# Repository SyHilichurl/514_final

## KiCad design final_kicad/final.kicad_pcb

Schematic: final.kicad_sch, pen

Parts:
BT1: Battery_Cell; JST_PH_B2B-PH-K_1x02_P2.00mm_Vertical
C1, C2: 0.1U; C_0603_1608Metric
C3: 2200PF; C_0603_1608Metric
C4: 10uF; C_0603_1608Metric
D1: LED; LED_D3.0mm
FSR1: 10K; PinHeader_1x02_P1.00mm_Vertical
J1: SDA; PinHeader_1x01_P1.00mm_Vertical
J2: SCL; PinHeader_1x01_P1.00mm_Vertical
J3: PIN1; PinHeader_1x01_P1.00mm_Vertical
J4: PIN2; PinHeader_1x01_P1.00mm_Vertical
J5: PIN3; PinHeader_1x01_P1.00mm_Vertical
J6: PIN4; PinHeader_1x01_P1.00mm_Vertical
J7: neg; PinHeader_1x01_P1.00mm_Vertical
J8: pos; PinHeader_1x01_P1.00mm_Vertical
M1: Motor_DC; PinHeader_1x02_P1.00mm_Vertical
Q1: NPN; Resonator-3Pin_W6.0mm_H3.0mm
R1, R2: 4.7K; R_0603_1608Metric
R3, R4: 10k; R_0603_1608Metric
R5: 200; R_0603_1608Metric
SW1: SW_Push; SW_PUSH_6mm
SW2: SW_SPST; SW_DIP_SPSTx01_Slide_6.7x4.1mm_W7.62mm_P2.54mm_LowProfile
U1: MPU-6050; InvenSense_QFN-24_4x4mm_P0.5mm

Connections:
+3V3: C2.2, M1.1 (+), R1.1, R2.1, R3.2, R4.2, U1.8 (VLOGIC), U1.13 (VDD)
GND: C1.1, C2.1, C3.2, D1.1 (K), FSR1.2, Q1.3 (E), SW1.2, U1.9 (AD0), U1.18 (GND)
unnamed: BT1.1 (+), C4.2
unnamed: BT1.2 (-), J7.1
unnamed: D1.2 (A), R5.2
unnamed: J1.1, R1.2, U1.24 (SDA)
unnamed: J2.1, R2.2, U1.23 (SCL)
unnamed: J3.1, R5.1
unnamed: FSR1.1, J4.1, R3.1
unnamed: J5.1, R4.1, SW1.1
unnamed: J6.1, Q1.2 (B)
unnamed: J8.1, SW2.1 (A)
unnamed: M1.2 (-), Q1.1 (C)
unnamed: C4.1, SW2.2 (B)
unnamed: C3.1, U1.20 (CPOUT)
unnamed: C1.2, U1.10 (REGOUT)

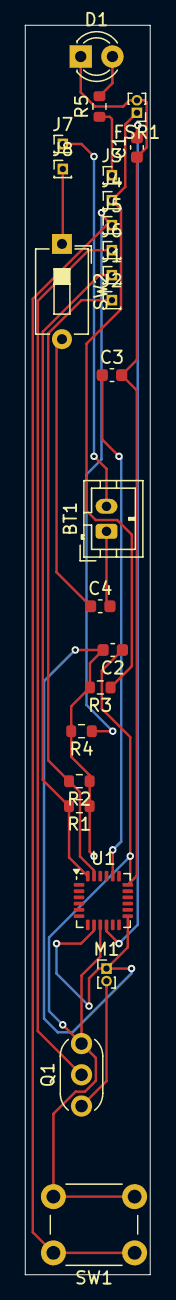
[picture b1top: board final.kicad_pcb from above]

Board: 2 copper layers, 10.0 x 100.0 mm, 25 parts (0 on the bottom side), 16 nets.

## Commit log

2025-01-22 images
2025-01-29 kicad
2025-01-29 line
2025-03-13 code
